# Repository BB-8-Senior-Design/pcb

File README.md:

# pcb
The main PCB - now without a charging circuit

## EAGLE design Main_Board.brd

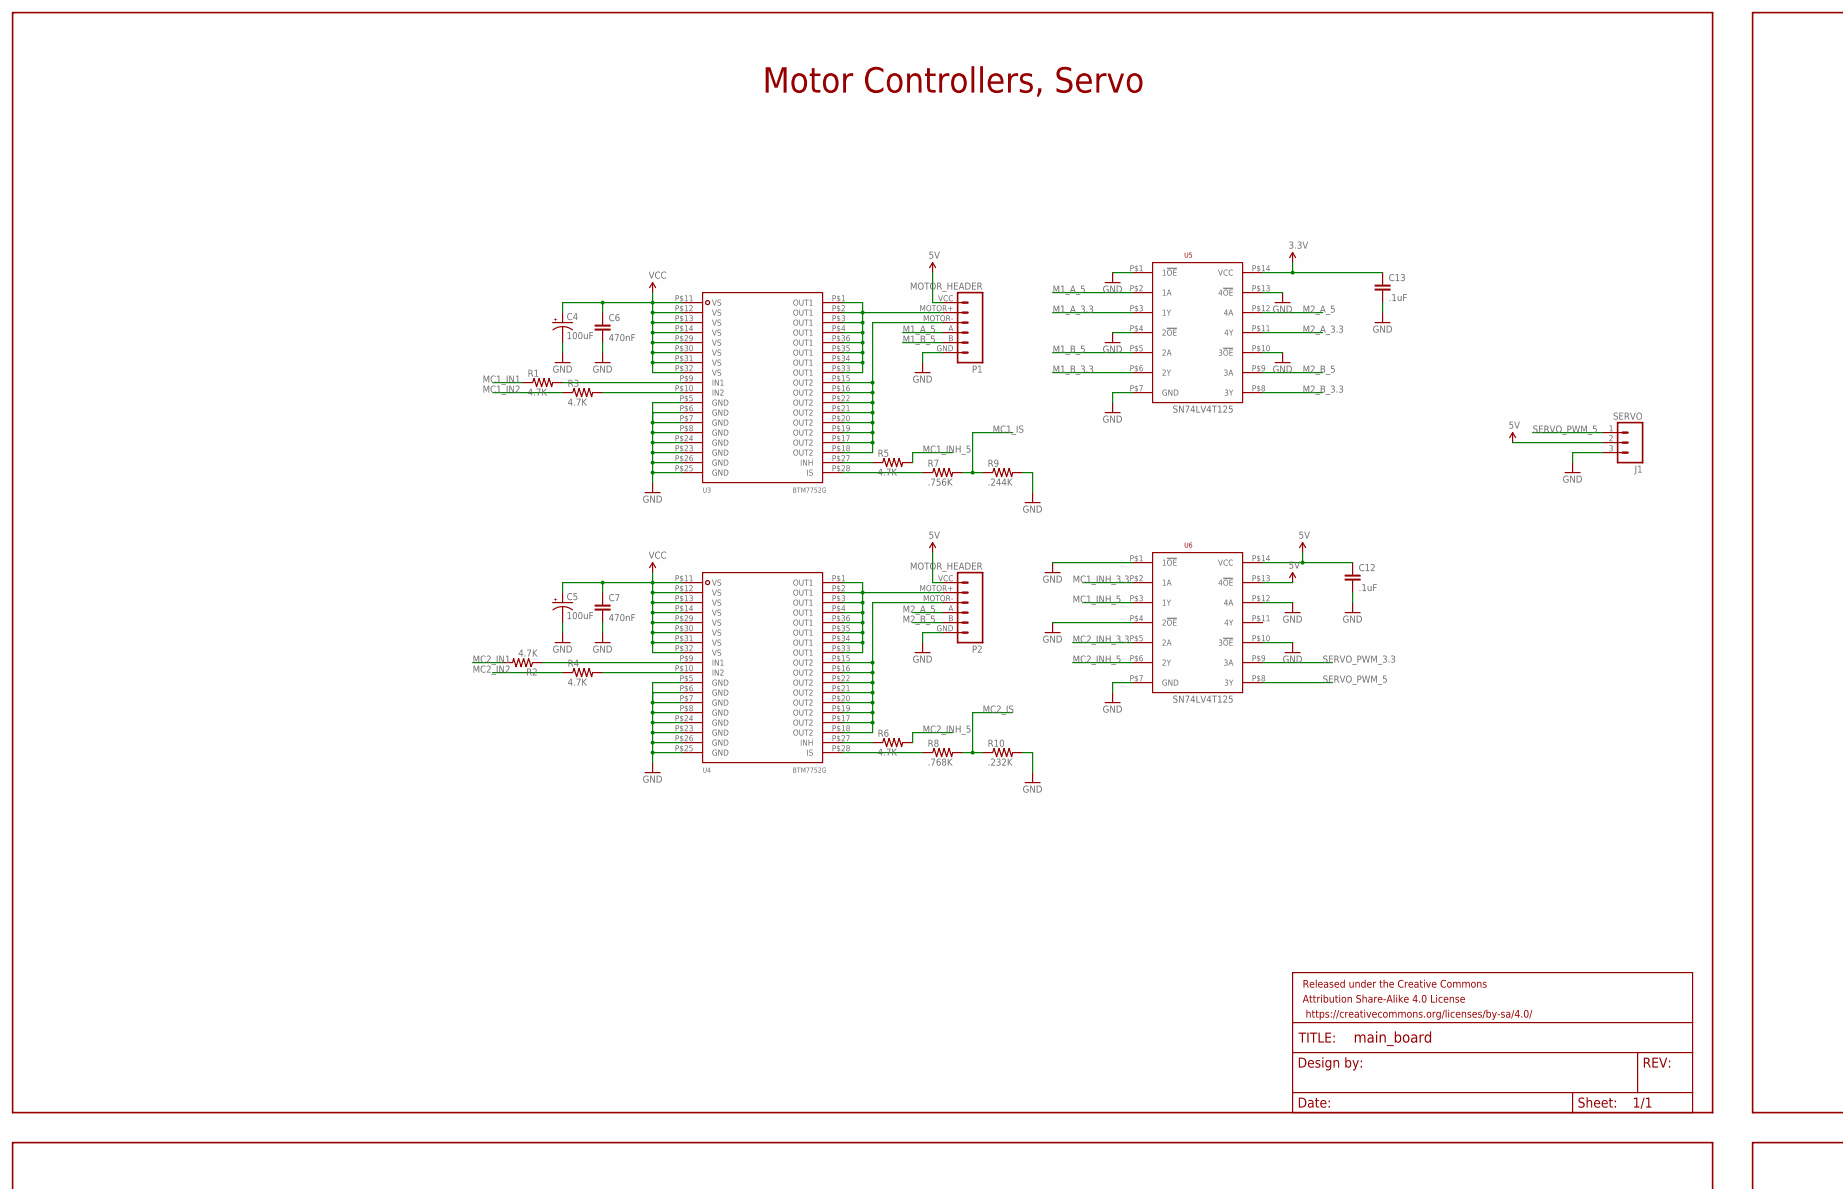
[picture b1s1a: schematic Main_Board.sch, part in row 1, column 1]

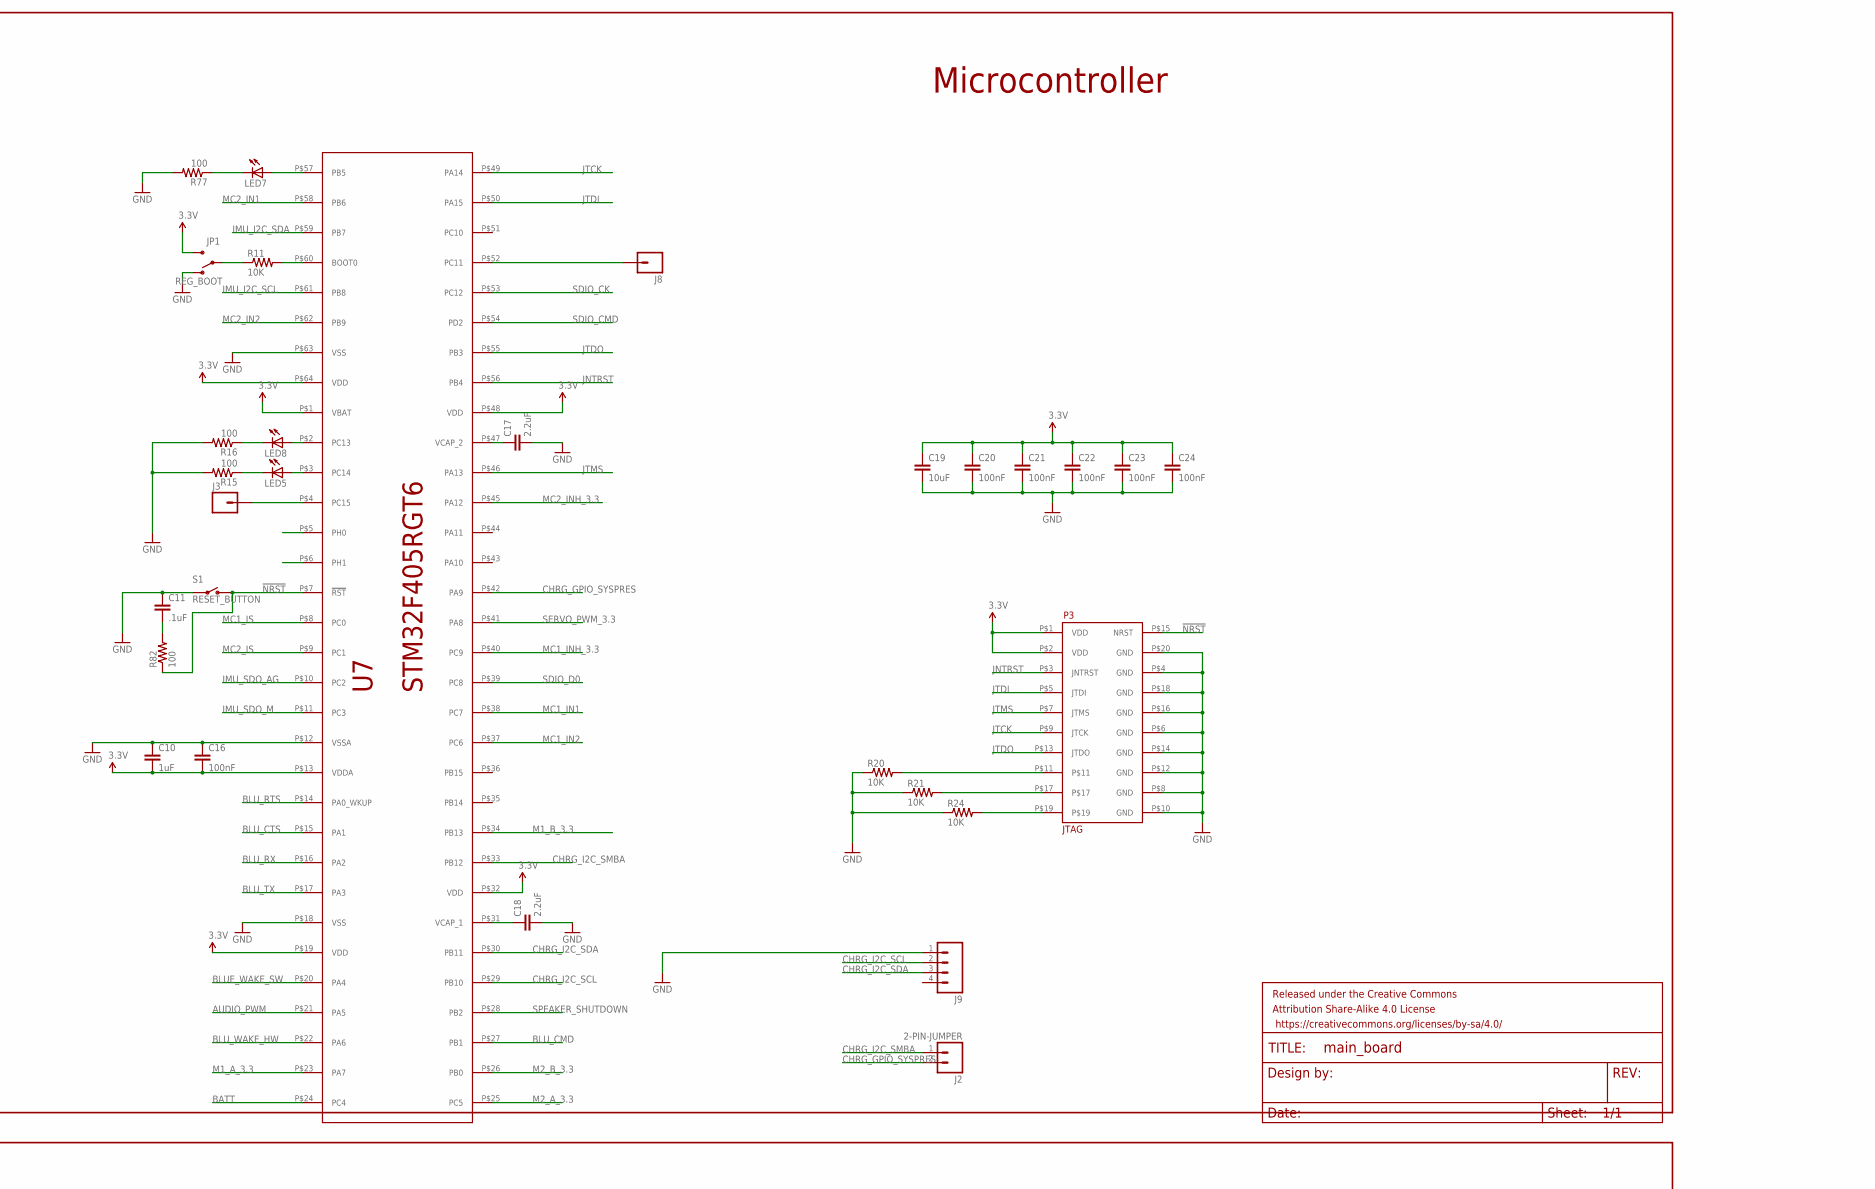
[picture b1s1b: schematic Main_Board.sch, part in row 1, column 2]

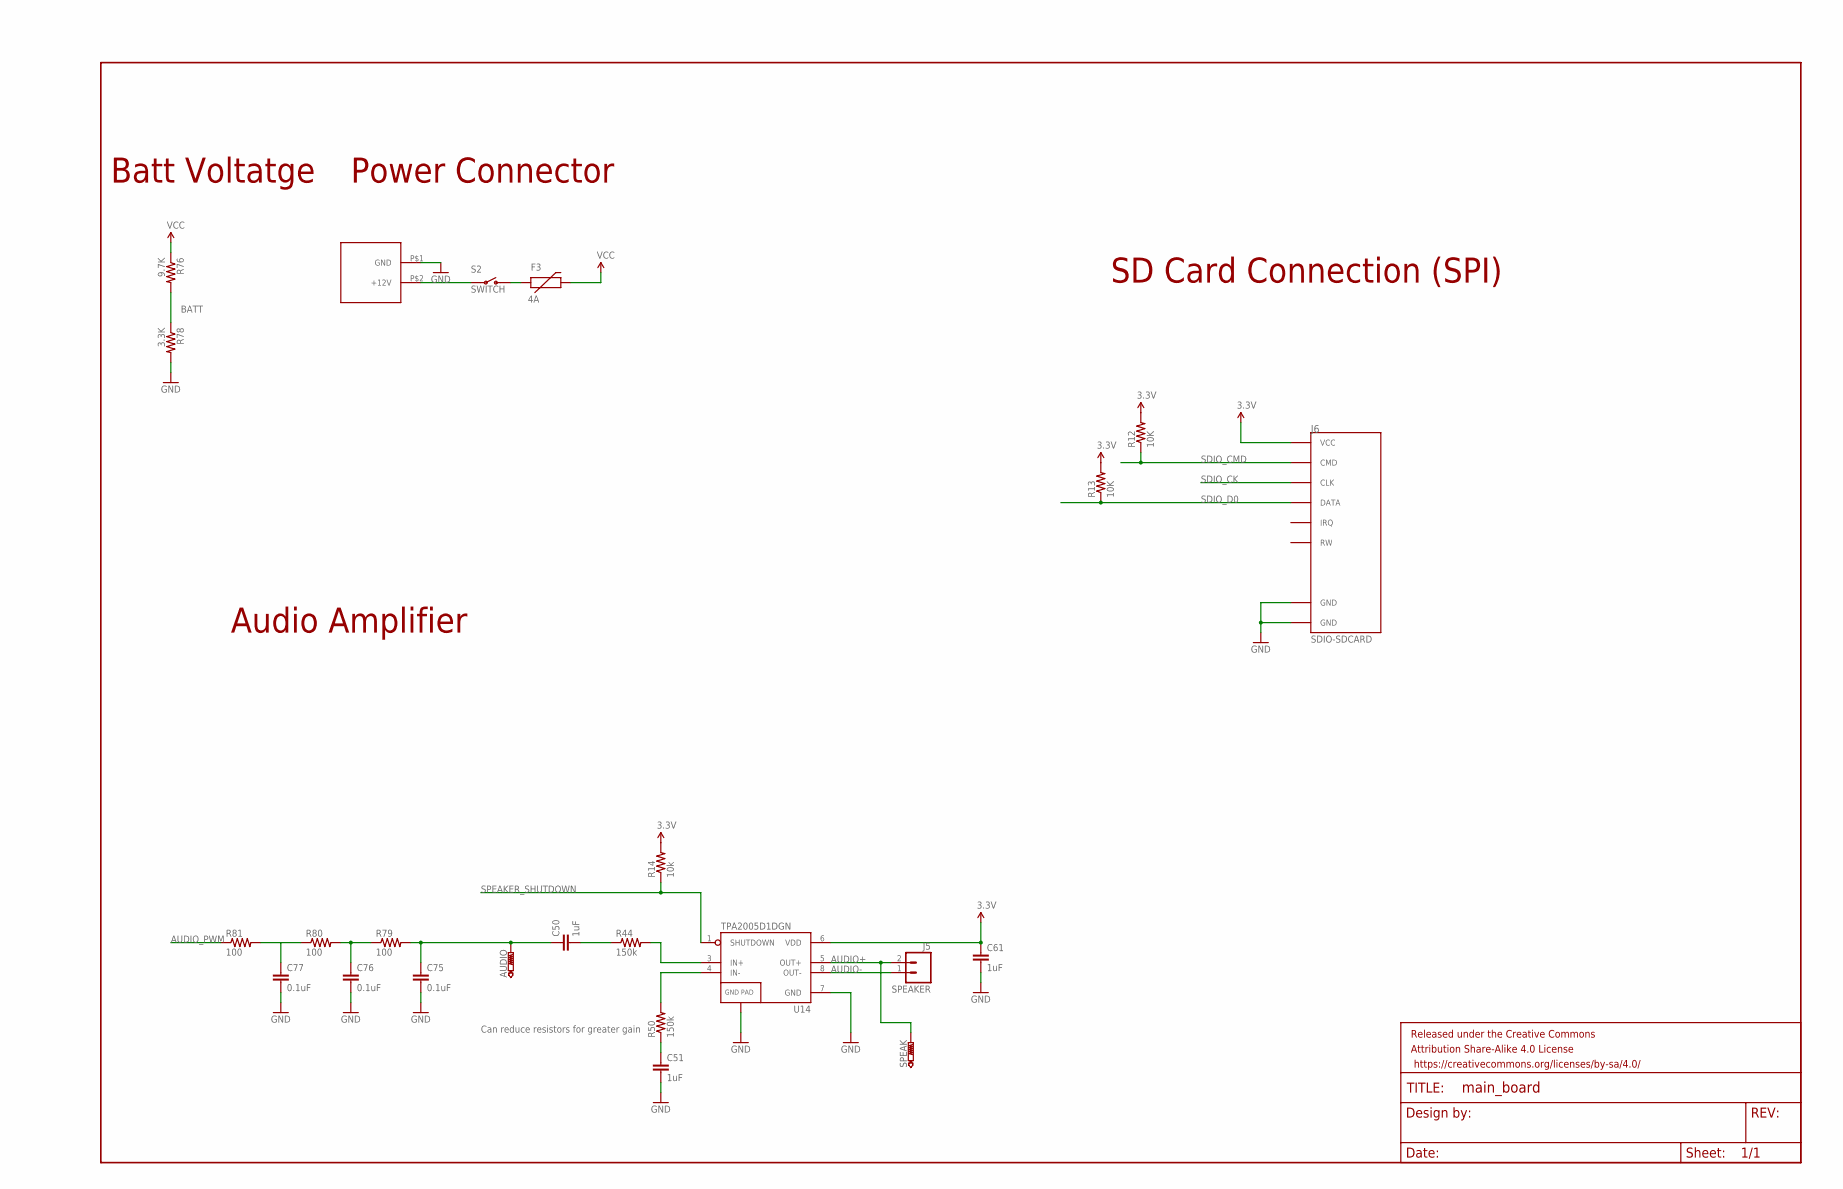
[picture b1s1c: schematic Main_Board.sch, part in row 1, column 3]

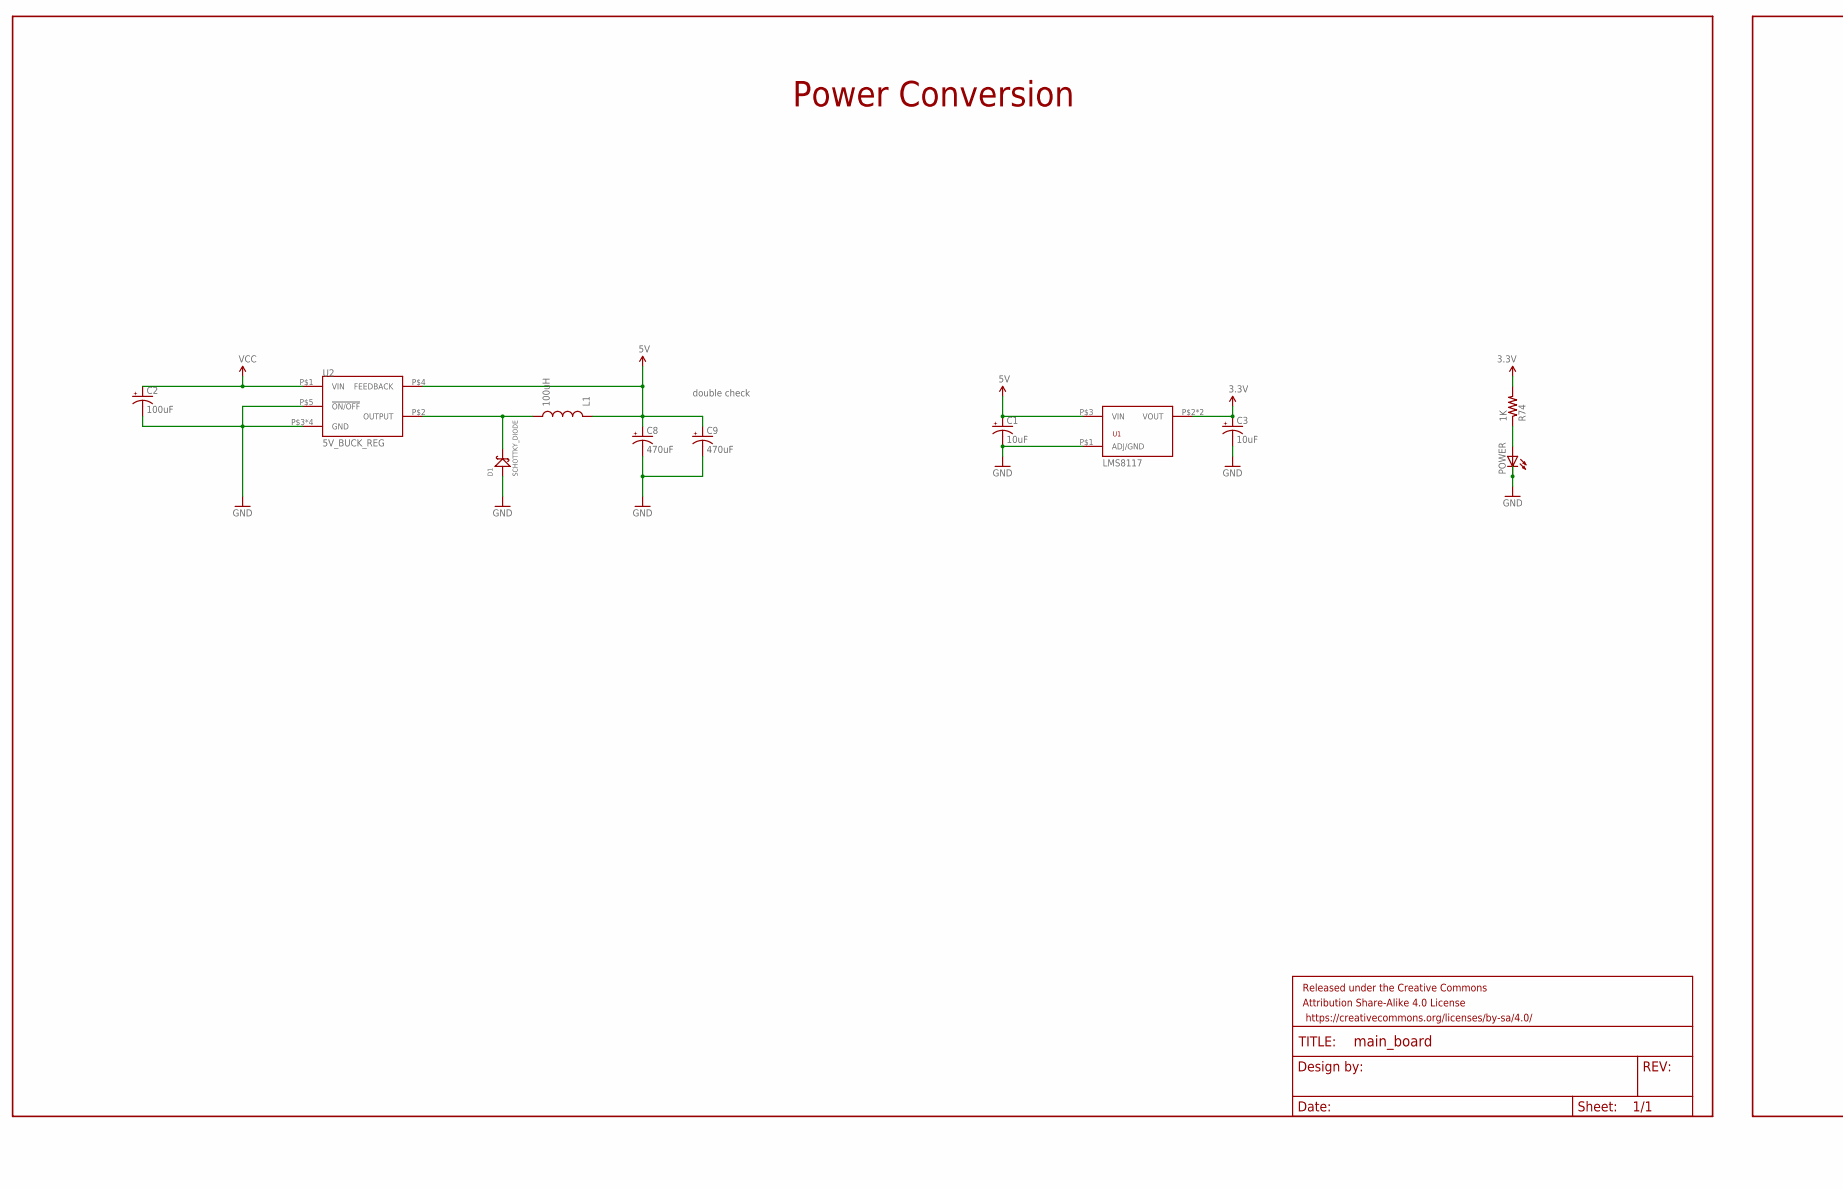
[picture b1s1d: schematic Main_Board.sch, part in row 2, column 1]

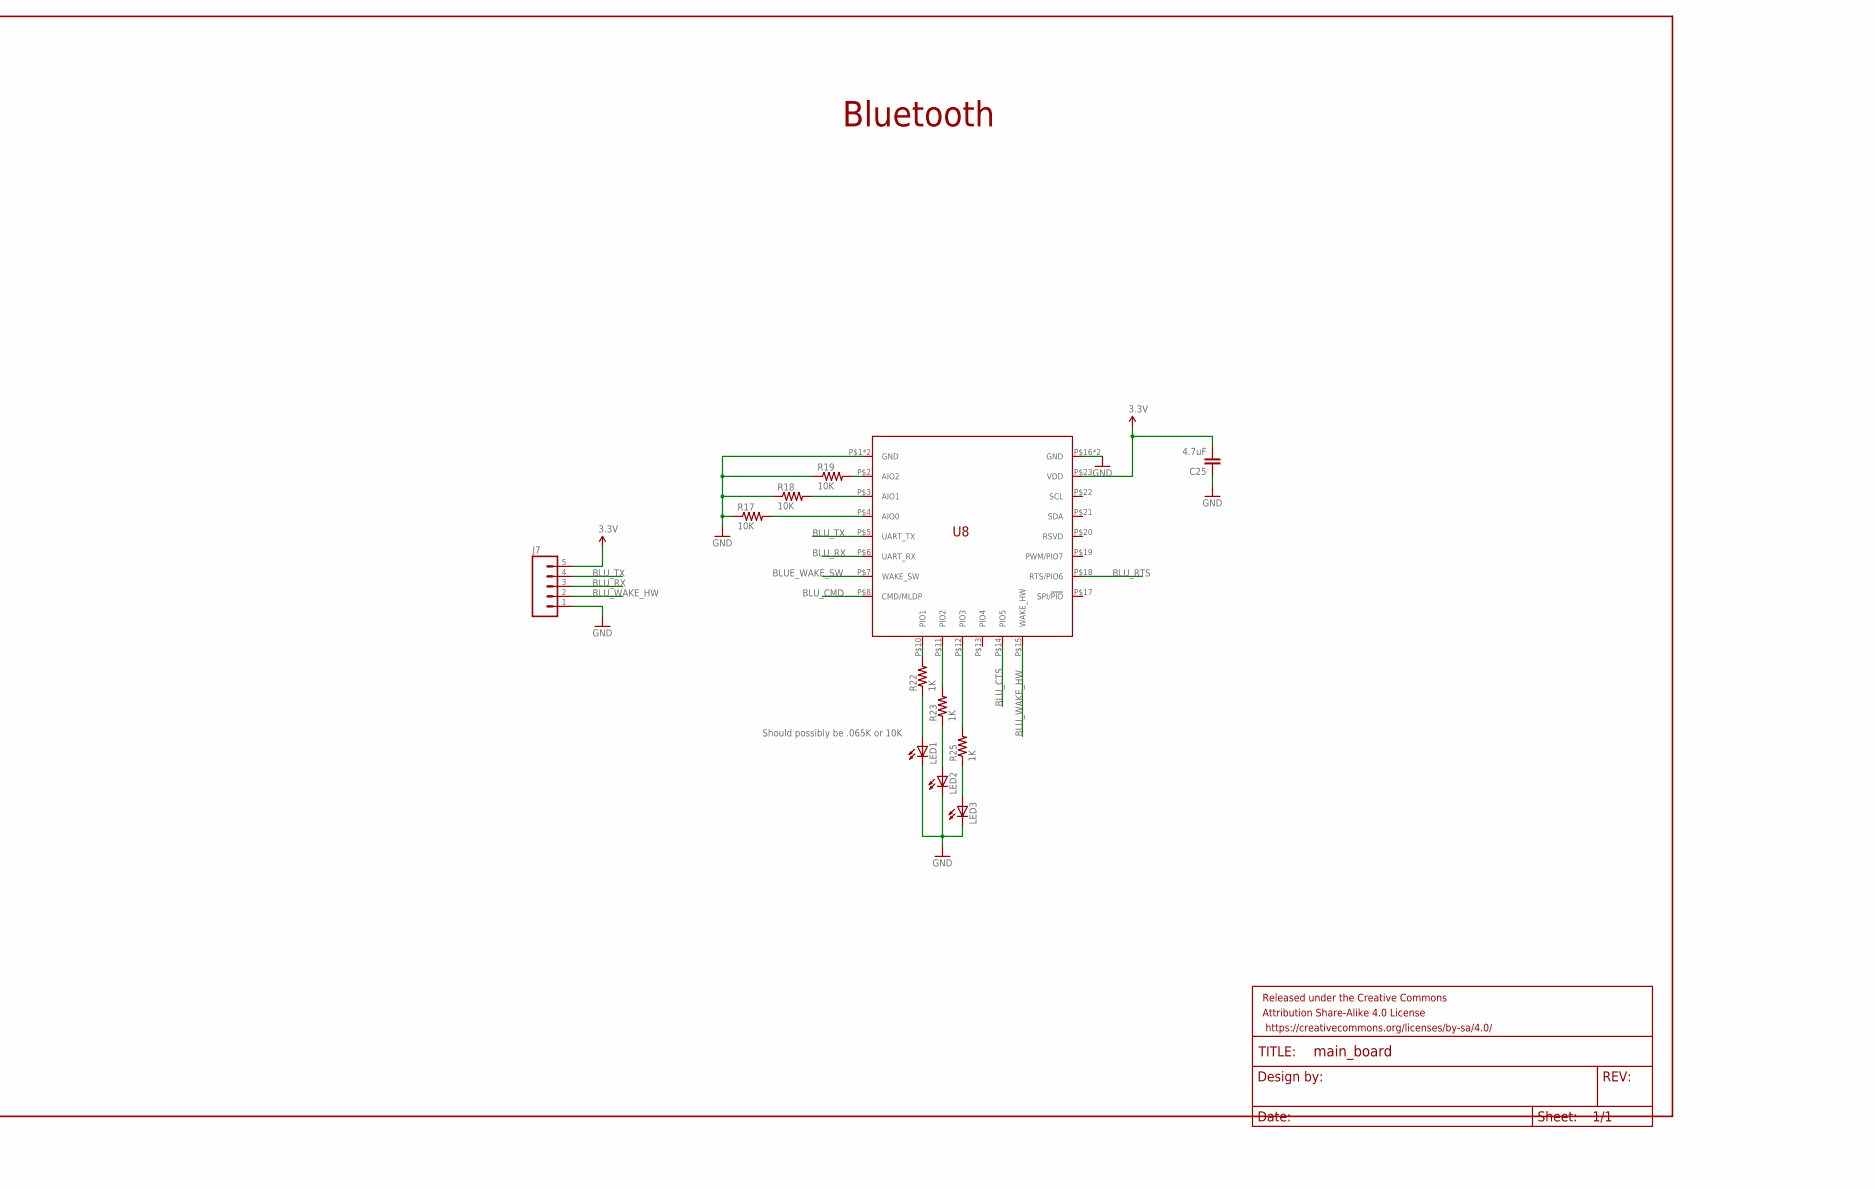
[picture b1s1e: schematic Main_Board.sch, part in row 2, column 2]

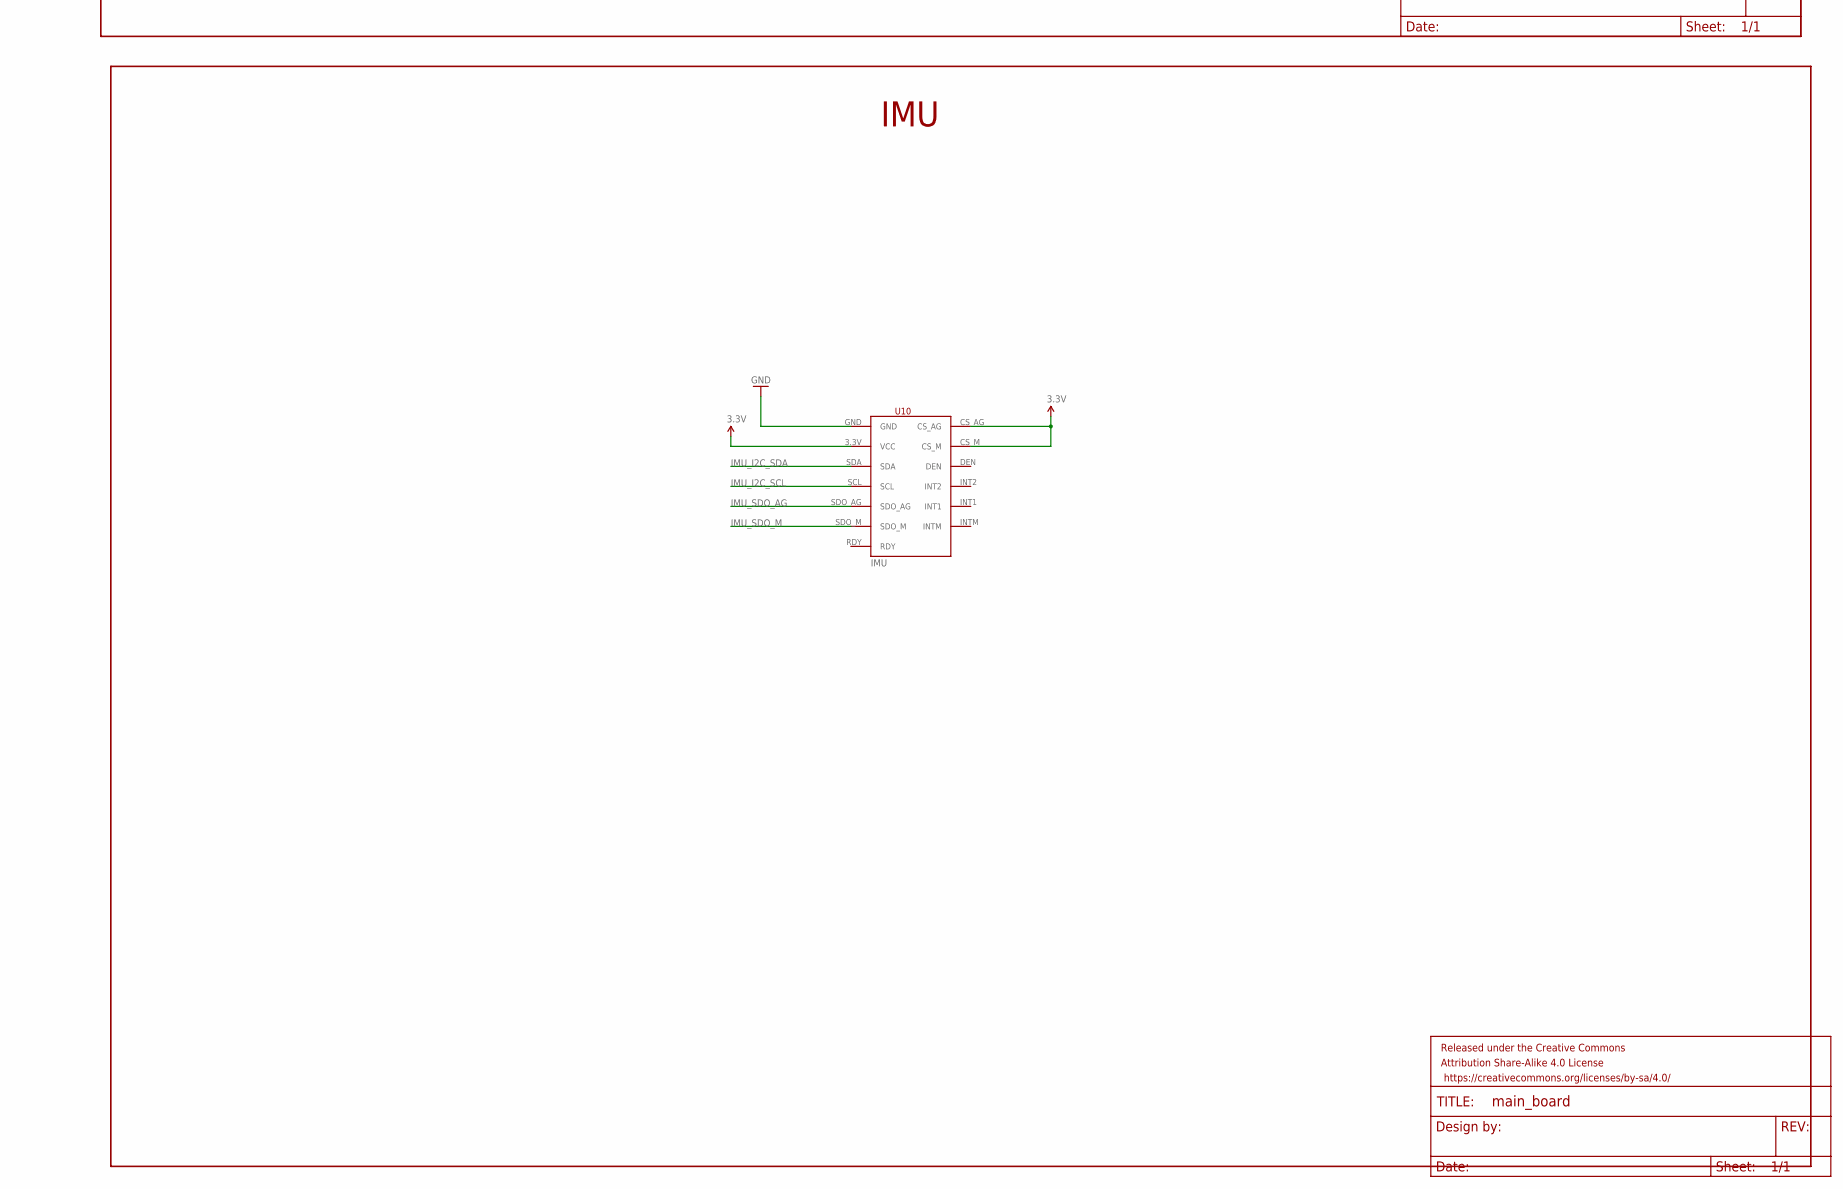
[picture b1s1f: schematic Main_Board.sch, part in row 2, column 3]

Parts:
AUDIO: PTR1B1,27; B1,27
C1, C3: 10uF; RADIAL_CAN_SMD-B
C2, C4, C5: 100uF; RADIAL_CAN_SMD-D8
C6, C7: 470nF; 0805
C8, C9: 470uF; RADIAL_CAN_SMD-G
C10, C50, C51, C61: 1uF; 0805
C11, C12, C13: .1uF; 0805
C16, C20, C21, C22, C23, C24: 100nF; 0805
C17, C18: 2.2uF; 0805
C19: 10uF; 0805
C25: 4.7uF; 0805
C75, C76, C77: 0.1uF; 0805
D1: SCHOTTKY_DIODE; DO-214AB2
F3: 4A; PTC-2920
FRAME3, FRAME4, FRAME5, FRAME6, FRAME7, FRAME8: FRAME-LEDGER; CREATIVE_COMMONS
J1: SERVO; 1X03
J2: 2-PIN-JUMPER; JST-2-PTH-VERT
J3, J8: M01PTH_NO_SILK_YES_STOP; 1X01_NO_SILK
J5: SPEAKER; JST-2-PTH-VERT
J6: SDIO-SDCARD; SD-5738
J7: M05PTH; 1X05
J9: M04POLAR; MOLEX-1X4
JP1: REG_BOOT; 1X03
L1: 100uH; SRN8040
LED1, LED2, LED3, LED5, LED7, LED8: LED1206; LED-1206
P1, P2: MOTOR_HEADER; 1X06
P3: JTAG; IDC20
POWER: LED1206; LED-1206
R1, R2, R3, R4, R5, R6: 4.7K; 0805
R7: .756K; 0805
R8: .768K; 0805
R9: .244K; 0805
R10: .232K; 0805
R11, R12, R13, R17, R18, R19, R20, R21, R24: 10K; 0805
R14: 10k; 0805
R15, R16, R77, R79, R80, R81, R82: 100; 0805
R22, R23, R25, R74: 1K; 0805
R44, R50: 150k; 0805
R76: 9.7K; 0805
R78: 3.3K; 0805
S1: RESET_BUTTON; 5.2X5.2
S2: SWITCH
SPEAK: PTR1B1,27; B1,27
U1: LMS8117; SOT-223
U2: 5V_BUCK_REG; T0-263-6
U3, U4: BTM7752G; 36-BSSOP
U5, U6: SN74LV4T125; 14-TSSOP
U7: STM32F405RGT6; LQFP64
U8: RN4020RN4020; RN4020
U10: IMU; IMU_BREAKOUT
U14: TPA2005D1DGN; POWER-SOP8
U$1: XT60

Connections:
3.3V: C3.P$1 (+), C10.2, C13.1, C16.2, C19.1, C20.1, C21.1, C22.1, C23.1, C24.1, C25.2, C61.1, J6.P$4 (VCC), J7.5, JP1.3 (S), P3.P$1 (VDD), P3.P$2 (VDD), R12.2, R13.2, R14.2, R74.2, U1.P$2 (VOUT), U1.P$4 (VOUT), U5.P$14 (VCC), U7.P$1 (VBAT), U7.P$13 (VDDA), U7.P$19 (VDD), U7.P$32 (VDD), U7.P$48 (VDD), U7.P$64 (VDD), U8.P$23 (VDD), U10.3.3V (VCC), U10.CS_AG, U10.CS_M, U14.6 (VDD)
5V: C1.P$1 (+), C8.P$1 (+), C9.P$1 (+), C12.1, J1.2, L1.P$1 (1), P1.VCC, P2.VCC, U1.P$3 (VIN), U2.P$4 (FEEDBACK), U6.P$13 (4!OE), U6.P$14 (VCC)
!NRST: P3.P$15 (NRST), R82.1, S1.P$1 (O), S1.P$2 (O), U7.P$7 (!RST)
AUDIO+: J5.2, SPEAK.TP, U14.5 (OUT+)
AUDIO-: J5.1, U14.8 (OUT-)
AUDIO_FILT_OUT: AUDIO.TP, C50.1, C75.1, R79.2
AUDIO_PWM: R81.1, U7.P$21 (PA5)
BATT: R76.2, R78.1, U7.P$24 (PC4)
BLUE_WAKE_SW: U7.P$20 (PA4), U8.P$7 (WAKE_SW)
BLU_CMD: U7.P$27 (PB1), U8.P$8 (CMD/MLDP)
BLU_CTS: U7.P$15 (PA1), U8.P$14 (PIO5)
BLU_RTS: U7.P$14 (PA0_WKUP), U8.P$18 (RTS/PIO6)
BLU_RX: J7.3, U7.P$16 (PA2), U8.P$6 (UART_RX)
BLU_TX: J7.4, U7.P$17 (PA3), U8.P$5 (UART_TX)
BLU_WAKE_HW: J7.2, U7.P$22 (PA6), U8.P$15 (WAKE_HW)
CHRG_GPIO_SYSPRES: J2.2, U7.P$42 (PA9)
CHRG_I2C_SCL: J9.2, U7.P$29 (PB10)
CHRG_I2C_SDA: J9.3, U7.P$30 (PB11)
CHRG_I2C_SMBA: J2.1, U7.P$33 (PB12)
GND: C1.P$2 (-), C2.P$2 (-), C3.P$2 (-), C4.P$2 (-), C5.P$2 (-), C6.2, C7.2, C8.P$2 (-), C9.P$2 (-), C10.1, C11.1, C12.2, C13.2, C16.1, C17.2, C18.2, C19.2, C20.2, C21.2, C22.2, C23.2, C24.2, C25.1, C51.2, C61.2, C75.2, C76.2, C77.2, D1.A, J1.3, J6.P$3 (GND), J6.P$6 (GND), J7.1, J9.1, JP1.1 (O), LED1.C, LED2.C, LED3.C, P1.GND, P2.GND, P3.P$4 (GND), P3.P$6 (GND), P3.P$8 (GND), P3.P$10 (GND), P3.P$12 (GND), P3.P$14 (GND), P3.P$16 (GND), P3.P$18 (GND), P3.P$20 (GND), POWER.C, R9.2, R10.2, R15.2, R16.2, R17.1, R18.1, R19.1, R20.1, R21.1, R24.1, R77.2, R78.2, S1.P$3, S1.P$4, U1.P$1 (ADJ/GND), U2.P$3 (GND), U2.P$5 (!ON/OFF), U2.P$6 (GND), U2.P$7 (GND), U2.P$8 (GND), U3.P$5 (GND), U3.P$6 (GND), U3.P$7 (GND), U3.P$8 (GND), U3.P$23 (GND), U3.P$24 (GND), U3.P$25 (GND), U3.P$26 (GND), U4.P$5 (GND), U4.P$6 (GND), U4.P$7 (GND), U4.P$8 (GND), U4.P$23 (GND), U4.P$24 (GND), U4.P$25 (GND), U4.P$26 (GND), U5.P$1 (1!OE), U5.P$4 (2!OE), U5.P$7 (GND), U5.P$10 (3!OE), U5.P$13 (4!OE), U6.P$1 (1!OE), U6.P$4 (2!OE), U6.P$7 (GND), U6.P$10 (3!OE), U6.P$12 (4A), U7.P$12 (VSSA), U7.P$18 (VSS), U7.P$63 (VSS), U8.P$1 (GND), U8.P$9 (GND), U8.P$16 (GND), U8.P$24 (GND), U10.GND, U14.7 (GND), U14.9 (GND), U$1.P$1 (GND)
IMU_I2C_SCL: U7.P$61 (PB8), U10.SCL
IMU_I2C_SDA: U7.P$59 (PB7), U10.SDA
IMU_SDO_AG: U7.P$10 (PC2), U10.SDO_AG
IMU_SDO_M: U7.P$11 (PC3), U10.SDO_M
JNTRST: P3.P$3 (JNTRST), U7.P$56 (PB4)
JTCK: P3.P$9 (JTCK), U7.P$49 (PA14)
JTDI: P3.P$5 (JTDI), U7.P$50 (PA15)
JTDO: P3.P$13 (JTDO), U7.P$55 (PB3)
JTMS: P3.P$7 (JTMS), U7.P$46 (PA13)
M1_A_3.3: U5.P$3 (1Y), U7.P$23 (PA7)
M1_A_5: P1.A, U5.P$2 (1A)
M1_B_3.3: U5.P$6 (2Y), U7.P$34 (PB13)
M1_B_5: P1.B, U5.P$5 (2A)
M2_A_3.3: U5.P$11 (4Y), U7.P$25 (PC5)
M2_A_5: P2.A, U5.P$12 (4A)
M2_B_3.3: U5.P$8 (3Y), U7.P$26 (PB0)
M2_B_5: P2.B, U5.P$9 (3A)
MC1_IN1: R1.1, U7.P$38 (PC7)
MC1_IN2: R3.1, U7.P$37 (PC6)
MC1_INH_3.3: U6.P$2 (1A), U7.P$40 (PC9)
MC1_INH_5: R5.2, U6.P$3 (1Y)
MC1_IS: R7.2, R9.1, U7.P$8 (PC0)
MC2_IN1: R2.2, U7.P$58 (PB6)
MC2_IN2: R4.1, U7.P$62 (PB9)
MC2_INH_3.3: U6.P$5 (2A), U7.P$45 (PA12)
MC2_INH_5: R6.2, U6.P$6 (2Y)
MC2_IS: R8.2, R10.1, U7.P$9 (PC1)
unnamed: P1.MOTOR+, U3.P$1 (OUT1), U3.P$2 (OUT1), U3.P$3 (OUT1), U3.P$4 (OUT1), U3.P$33 (OUT1), U3.P$34 (OUT1), U3.P$35 (OUT1), U3.P$36 (OUT1)
unnamed: P1.MOTOR-, U3.P$15 (OUT2), U3.P$16 (OUT2), U3.P$17 (OUT2), U3.P$18 (OUT2), U3.P$19 (OUT2), U3.P$20 (OUT2), U3.P$21 (OUT2), U3.P$22 (OUT2)
unnamed: R1.2, U3.P$9 (IN1)
unnamed: R3.2, U3.P$10 (IN2)
unnamed: R7.1, U3.P$28 (IS)
unnamed: R5.1, U3.P$27 (INH)
unnamed: R19.2, U8.P$2 (AIO2)
unnamed: P2.MOTOR+, U4.P$1 (OUT1), U4.P$2 (OUT1), U4.P$3 (OUT1), U4.P$4 (OUT1), U4.P$33 (OUT1), U4.P$34 (OUT1), U4.P$35 (OUT1), U4.P$36 (OUT1)
unnamed: P2.MOTOR-, U4.P$15 (OUT2), U4.P$16 (OUT2), U4.P$17 (OUT2), U4.P$18 (OUT2), U4.P$19 (OUT2), U4.P$20 (OUT2), U4.P$21 (OUT2), U4.P$22 (OUT2)
unnamed: R2.1, U4.P$9 (IN1)
unnamed: R4.2, U4.P$10 (IN2)
unnamed: LED5.C, R15.1
unnamed: R8.1, U4.P$28 (IS)
unnamed: R6.1, U4.P$27 (INH)
unnamed: C17.1, U7.P$47 (VCAP_2)
unnamed: C18.1, U7.P$31 (VCAP_1)
unnamed: J3.1, U7.P$4 (PC15)
unnamed: R11.2, U7.P$60 (BOOT0)
unnamed: JP1.2, R11.1
unnamed: P3.P$11, R20.2
unnamed: P3.P$17, R21.2
unnamed: P3.P$19, R24.2
unnamed: F3.1, S2.P$4 (O)
unnamed: R17.2, U8.P$4 (AIO0)
unnamed: LED5.A, U7.P$3 (PC14)
unnamed: D1.C, L1.P$2 (2), U2.P$2 (OUTPUT)
unnamed: S2.P$3, U$1.P$2 (+12V)
unnamed: R22.2, U8.P$10 (PIO1)
unnamed: LED1.A, R22.1
unnamed: R23.2, U8.P$11 (PIO2)
unnamed: R25.2, U8.P$12 (PIO3)
unnamed: LED2.A, R23.1
unnamed: LED3.A, R25.1
unnamed: LED8.A, U7.P$2 (PC13)
unnamed: POWER.A, R74.1
unnamed: J8.1, U7.P$52 (PC11)
unnamed: C77.1, R80.1, R81.2
unnamed: C76.1, R79.1, R80.2
unnamed: R18.2, U8.P$3 (AIO1)
unnamed: R50.2, U14.4 (IN-)
unnamed: C50.2, R44.1
unnamed: C51.1, R50.1
unnamed: R44.2, U14.3 (IN+)
unnamed: LED8.C, R16.1
unnamed: C11.2, R82.2
unnamed: LED7.A, U7.P$57 (PB5)
unnamed: LED7.C, R77.1
SDIO_CK: J6.P$5 (CLK), U7.P$53 (PC12)
SDIO_CMD: J6.P$2 (CMD), R12.1, U7.P$54 (PD2)
SDIO_D0: J6.P$7 (DATA), R13.1, U7.P$39 (PC8)
SERVO_PWM_3.3: U6.P$9 (3A), U7.P$41 (PA8)
SERVO_PWM_5: J1.1, U6.P$8 (3Y)
SPEAKER_SHUTDOWN: R14.1, U7.P$28 (PB2), U14.1 (SHUTDOWN)
VCC: C2.P$1 (+), C4.P$1 (+), C5.P$1 (+), C6.1, C7.1, F3.2, R76.1, U2.P$1 (VIN), U3.P$11 (VS), U3.P$12 (VS), U3.P$13 (VS), U3.P$14 (VS), U3.P$29 (VS), U3.P$30 (VS), U3.P$31 (VS), U3.P$32 (VS), U4.P$11 (VS), U4.P$12 (VS), U4.P$13 (VS), U4.P$14 (VS), U4.P$29 (VS), U4.P$30 (VS), U4.P$31 (VS), U4.P$32 (VS)

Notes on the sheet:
Motor Controllers, Servo
Microcontroller
Power Conversion
Bluetooth
double check
Audio Amplifier
SD Card Connection (SPI)
Should possibly be .065K or 10K
IMU
Can reduce resistors for greater gain
Power Connector
Batt Voltatge

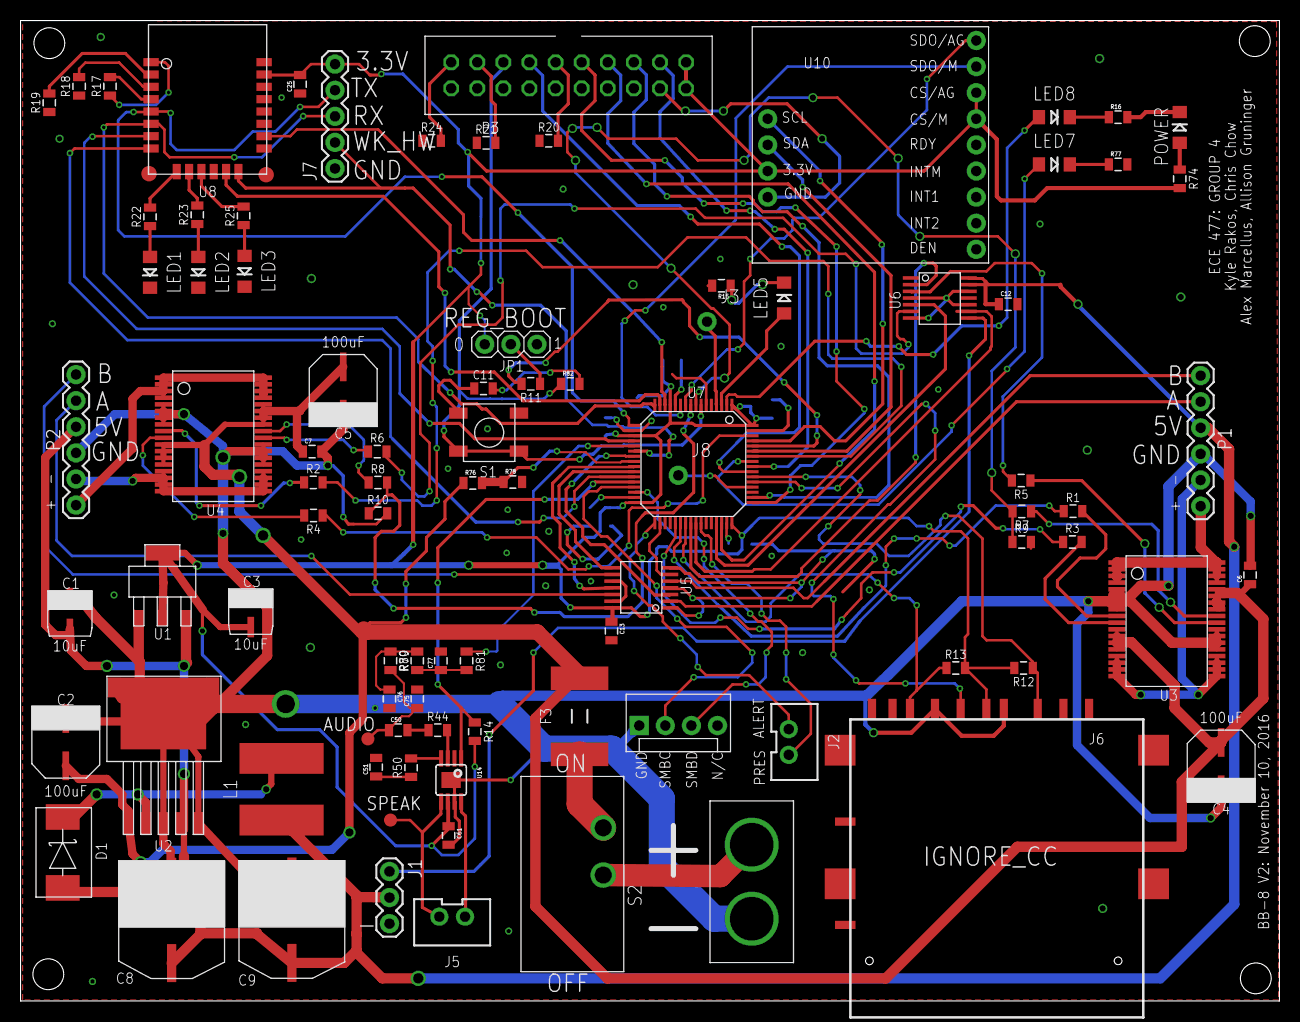
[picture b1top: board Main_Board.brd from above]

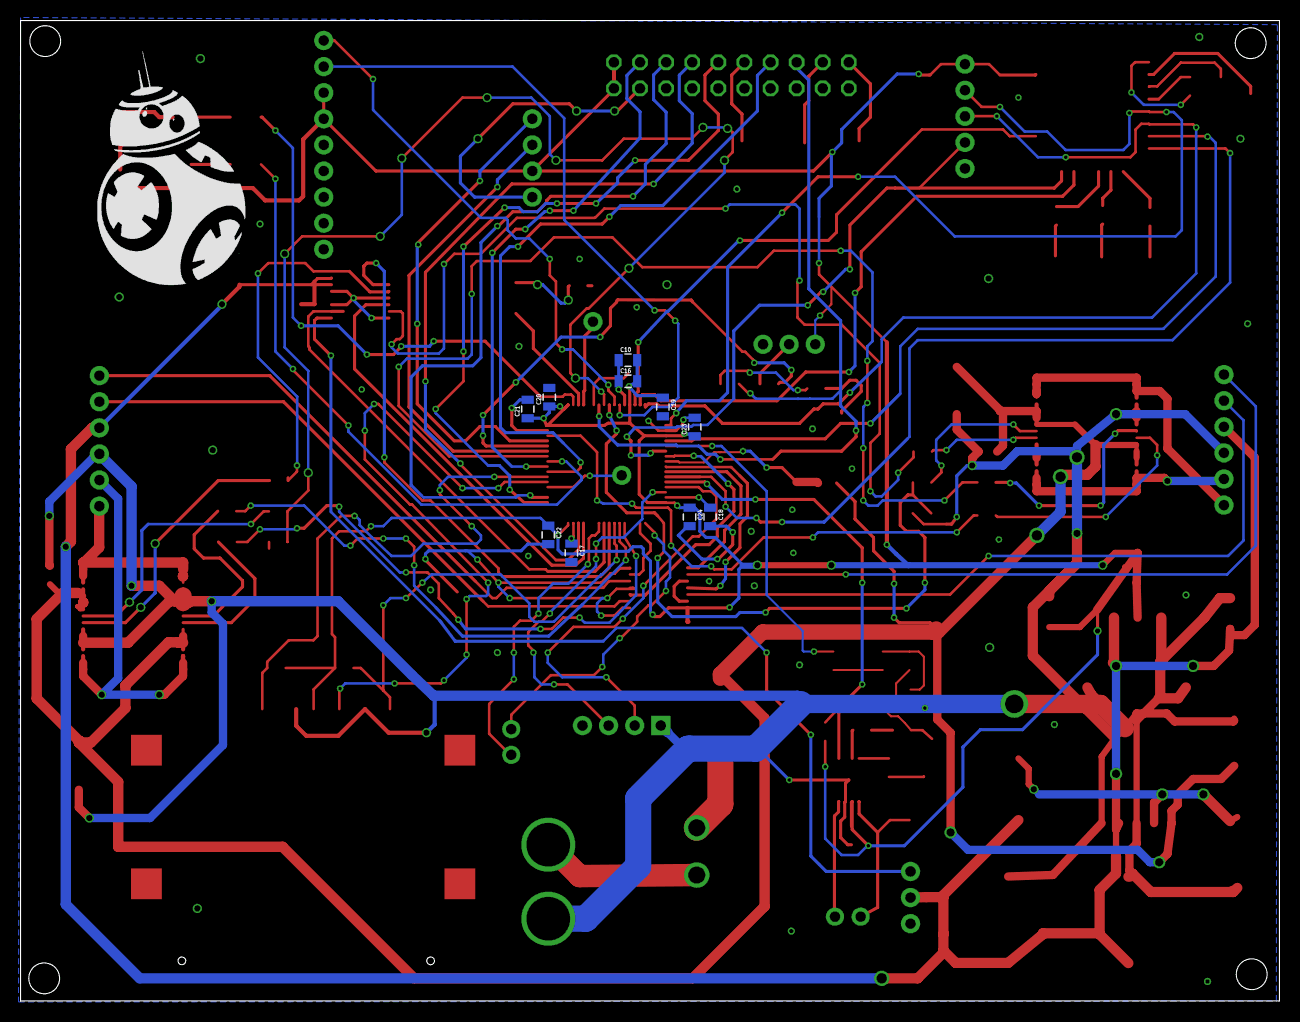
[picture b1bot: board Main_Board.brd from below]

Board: 2 copper layers, 122.5 x 95.4 mm, 107 parts (10 on the bottom side), 101 nets.

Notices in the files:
parts and their libraries:
SparkFun-Capacitors: Licensing: Creative Commons ShareAlike 4.0 International - https://creativecommons.org/licenses/by-sa/4.0
SparkFun-Aesthetics: Released under the Creative Commons Attribution Share-Alike 4.0 License
SparkFun-Aesthetics: https://creativecommons.org/licenses/by-sa/4.0
